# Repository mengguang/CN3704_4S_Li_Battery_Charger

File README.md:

# CN3704_4S_Li_Battery_Charger, Version 3
4S Li Battery charger using CN3704

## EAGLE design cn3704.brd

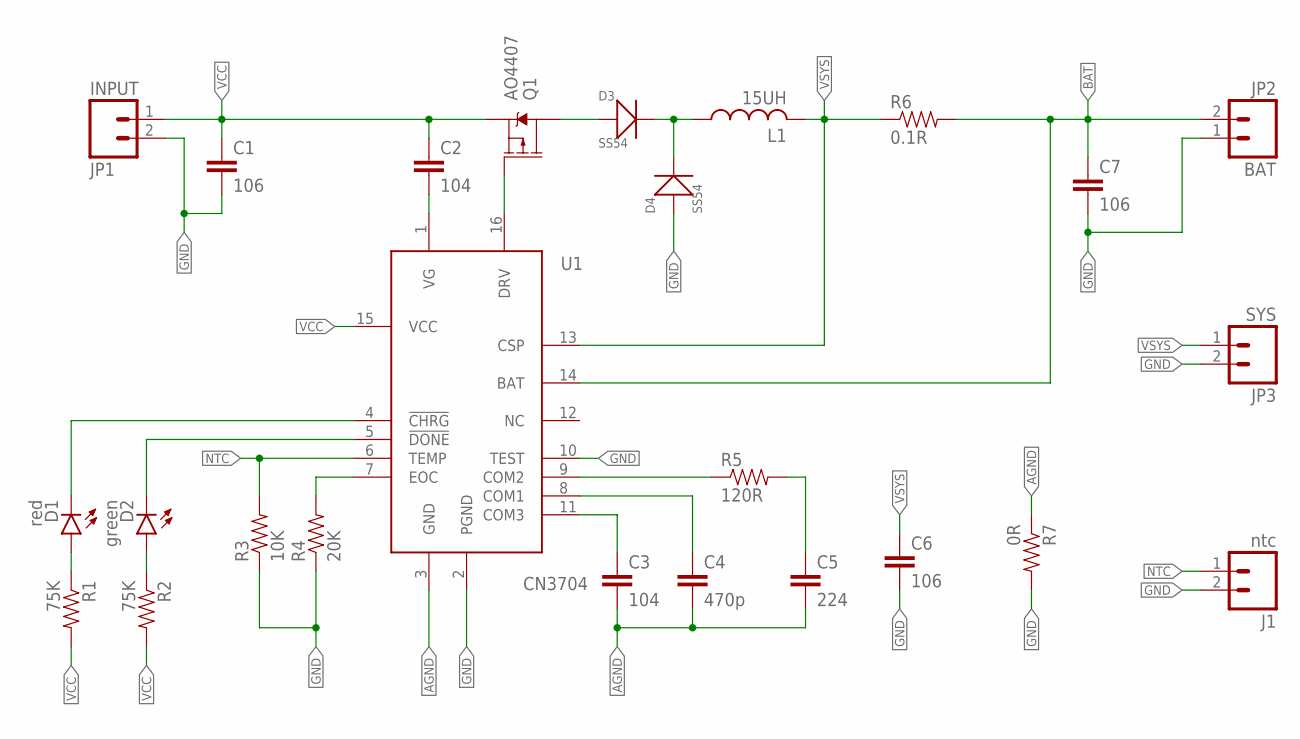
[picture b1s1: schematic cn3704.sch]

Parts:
C1, C6, C7: 106; 1206
C2: 104; 0603-CAP
C3: 104; C0402
C4: 470p; C0402
C5: 224; C0402
D1: red; LED-0603-SEEED
D2: green; LED-0603-SEEED
D3: SS54; DO-214AB
D4: SS54; DO-214AC
J1: ntc; 1X02_NO_SILK
JP1: INPUT; SCREWTERMINAL-5MM-2
JP2: BAT; SCREWTERMINAL-5MM-2
JP3: SYS; SCREWTERMINAL-5MM-2
L1: 15UH; L_SMDRI-127
Q1: AO4407; SO08
R1, R2: 75K; R0402
R3: 10K; R0402
R4: 20K; R0402
R5: 120R; R0402
R6: 0.1R; R2512
R7: 0R; R0402
U1: CN3704; TSSOP16

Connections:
AGND: C3.2, C4.2, C5.2, R7.1, U1.3 (GND)
BAT: C7.1, JP2.2, R6.2, U1.14 (BAT)
GND: C1.2, C6.2, C7.2, D4.1 (+), J1.2, JP1.2, JP2.1, JP3.2, R3.1, R4.1, R7.2, U1.2 (PGND), U1.10 (TEST)
unnamed: C2.2, U1.1 (VG)
unnamed: D1.- (C), U1.4 (!CHRG)
unnamed: D2.- (C), U1.5 (!DONE)
unnamed: D1.+ (A), R1.1
unnamed: D2.+ (A), R2.1
unnamed: R4.2, U1.7 (EOC)
unnamed: C3.1, U1.11 (COM3)
unnamed: C4.1, U1.8 (COM1)
unnamed: Q1.4 (G), U1.16 (DRV)
unnamed: R5.1, U1.9 (COM2)
unnamed: C5.1, R5.2
NTC: J1.1, R3.2, U1.6 (TEMP)
SW1: D3.1 (+), Q1.5 (D), Q1.6 (D), Q1.7 (D), Q1.8 (D)
SW2: D3.2 (-), D4.2 (-), L1.1
VCC: C1.1, C2.1, JP1.1, Q1.1 (S), Q1.2 (S), Q1.3 (S), R1.2, R2.2, U1.15 (VCC)
VSYS: C6.1, JP3.1, L1.2, R6.1, U1.13 (CSP)

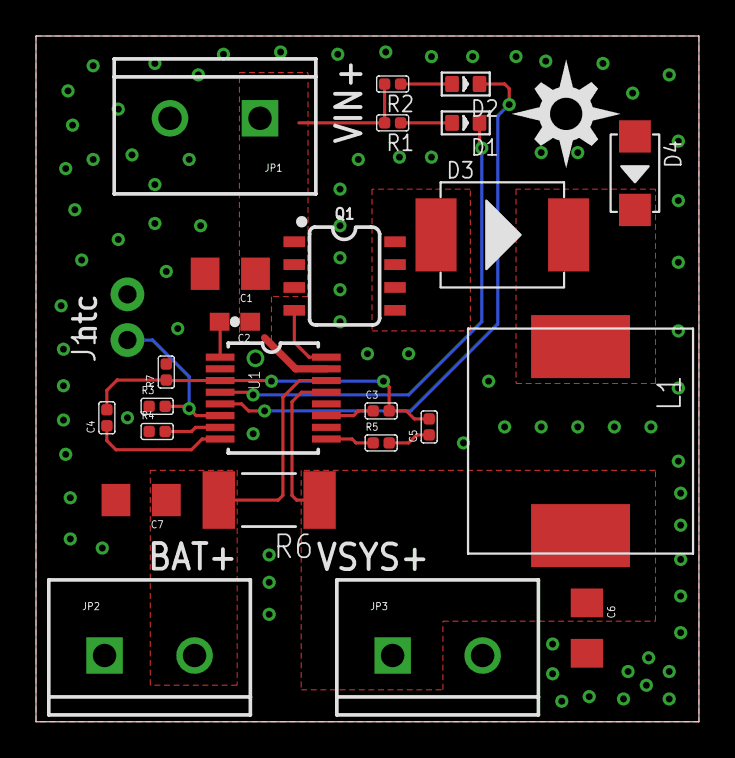
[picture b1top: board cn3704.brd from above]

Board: 2 copper layers, 36.8 x 38.1 mm, 26 parts (0 on the bottom side), 19 nets.

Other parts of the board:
U$1: DIYNOVA_LOGO

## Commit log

2017-10-31 Add files via upload
    version 3

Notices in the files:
parts and their libraries:
SparkFun-Connectors: Licensing: Creative Commons ShareAlike 4.0 International - https://creativecommons.org/licenses/by-sa/4.0
